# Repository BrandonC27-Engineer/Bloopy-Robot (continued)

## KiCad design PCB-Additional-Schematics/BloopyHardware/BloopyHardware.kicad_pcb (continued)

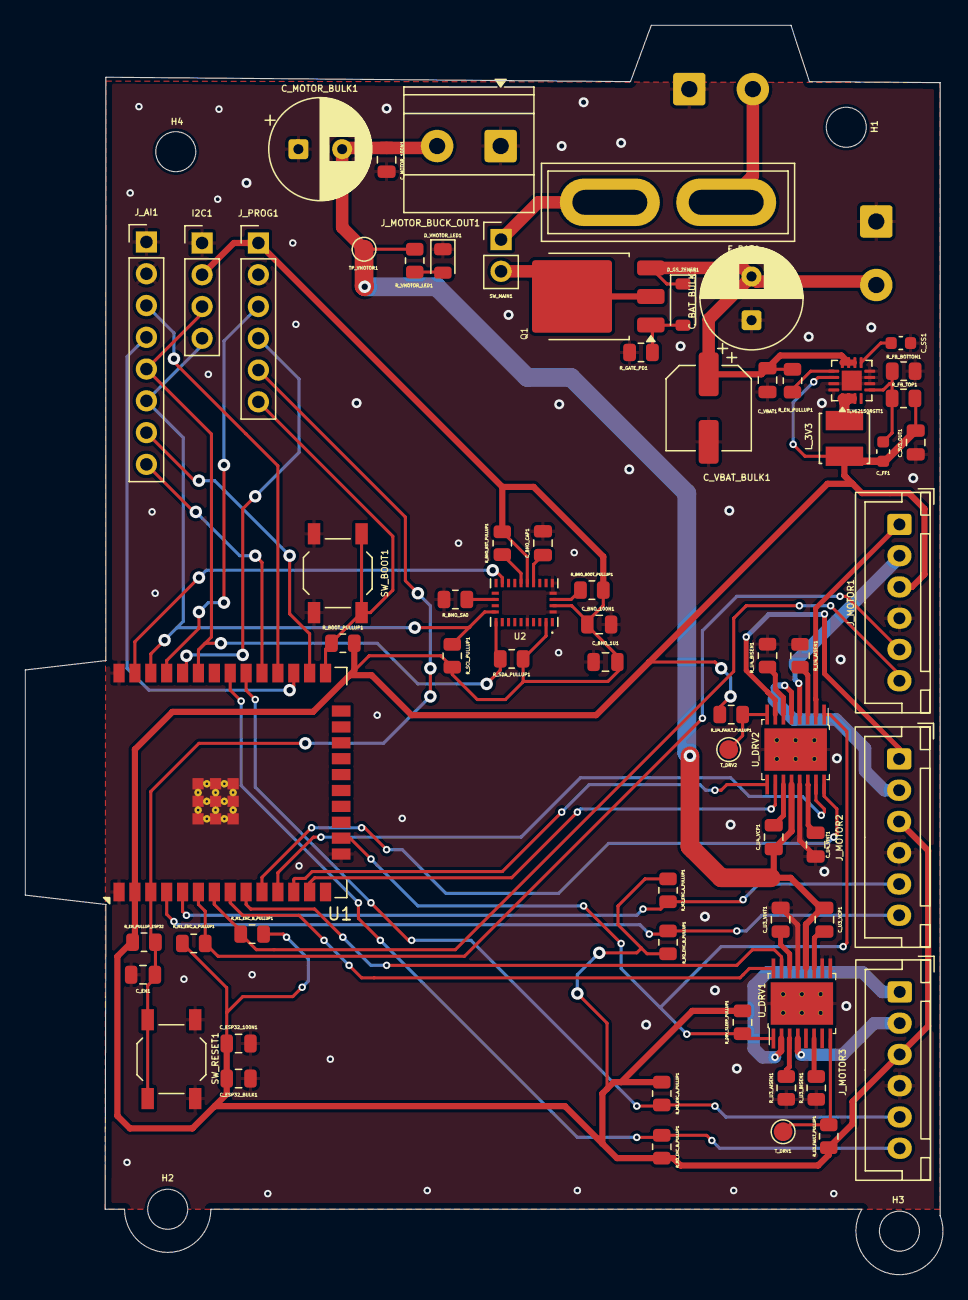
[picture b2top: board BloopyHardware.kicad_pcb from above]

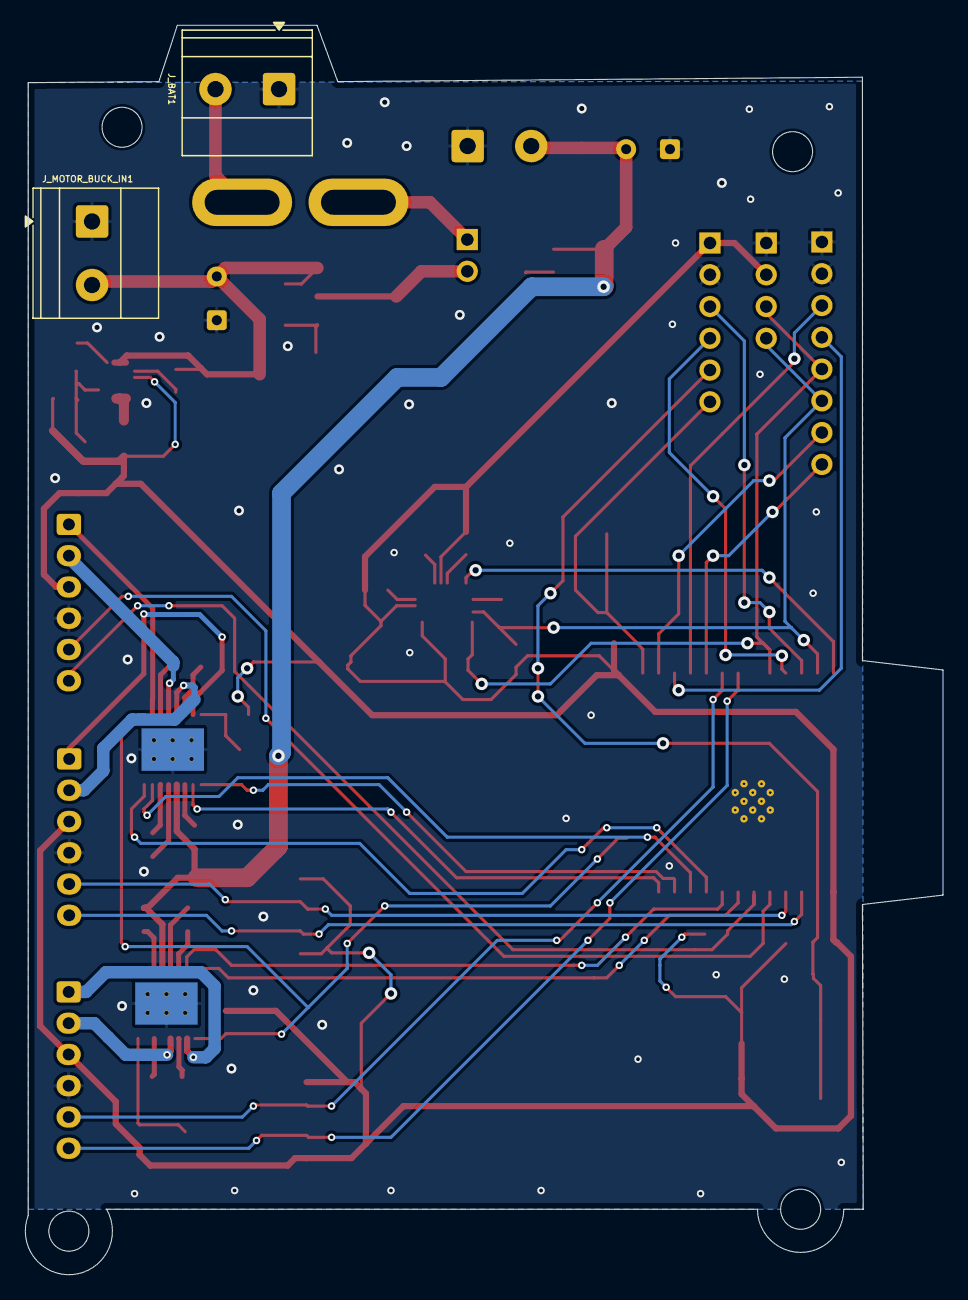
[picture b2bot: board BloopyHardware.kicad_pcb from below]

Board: 2 copper layers, 73.4 x 99.9 mm, 72 parts (2 on the bottom side), 57 nets.
